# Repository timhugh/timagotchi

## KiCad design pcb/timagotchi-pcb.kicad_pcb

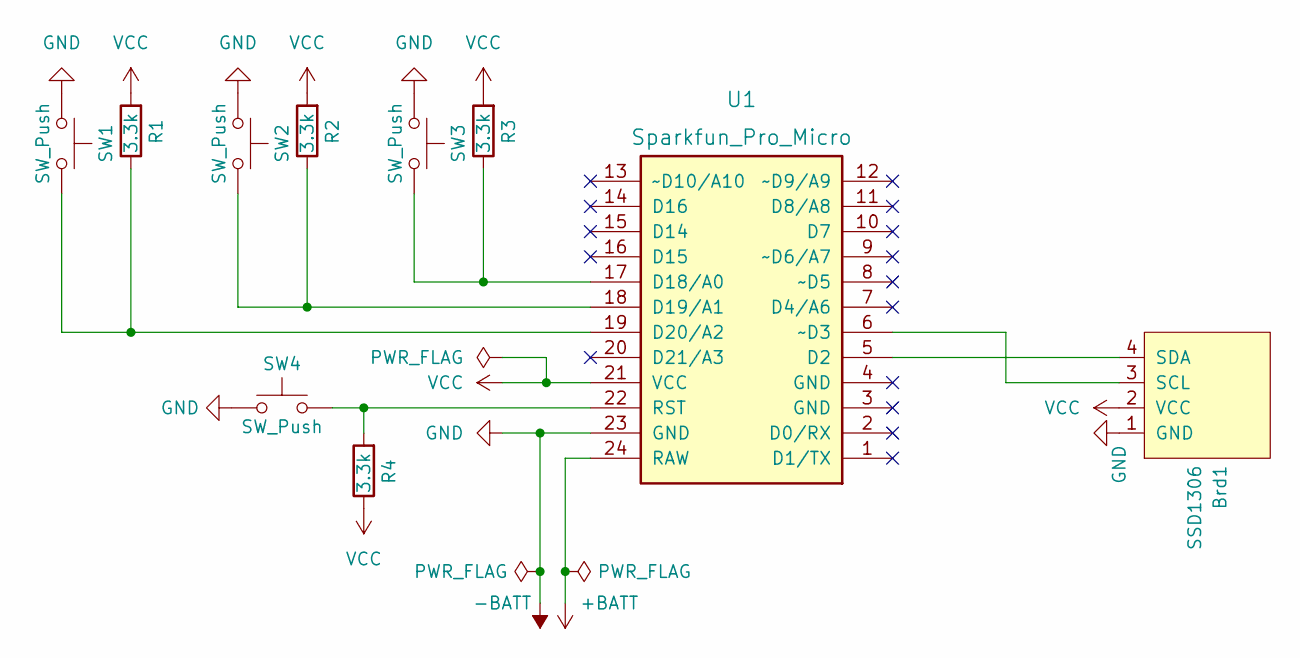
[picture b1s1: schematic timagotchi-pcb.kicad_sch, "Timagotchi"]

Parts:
Brd1: SSD1306; Adafruit_SSD1306_No_Mounting_Holes
R1, R2, R3, R4: 3.3k; R_0805_2012Metric
SW1, SW2, SW3, SW4: SW_Push; SW_PUSH_6mm
U1: Sparkfun_Pro_Micro

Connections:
+BATT: U1.24 (RAW)
-BATT: Brd1.1 (GND), SW1.2, SW2.2, SW3.2, SW4.2, U1.23 (GND)
unnamed: Brd1.3 (SCL), U1.6 (~D3)
unnamed: Brd1.4 (SDA), U1.5 (D2)
unnamed: R1.1, SW1.1, U1.19 (D20/A2)
unnamed: R2.1, SW2.1, U1.18 (D19/A1)
unnamed: R3.1, SW3.1, U1.17 (D18/A0)
unnamed: R4.2, SW4.1, U1.22 (RST)
VCC: Brd1.2 (VCC), R1.2, R2.2, R3.2, R4.1, U1.21 (VCC)

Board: 2 copper layers, 10 parts (0 on the bottom side), 8 nets, no tracks yet.

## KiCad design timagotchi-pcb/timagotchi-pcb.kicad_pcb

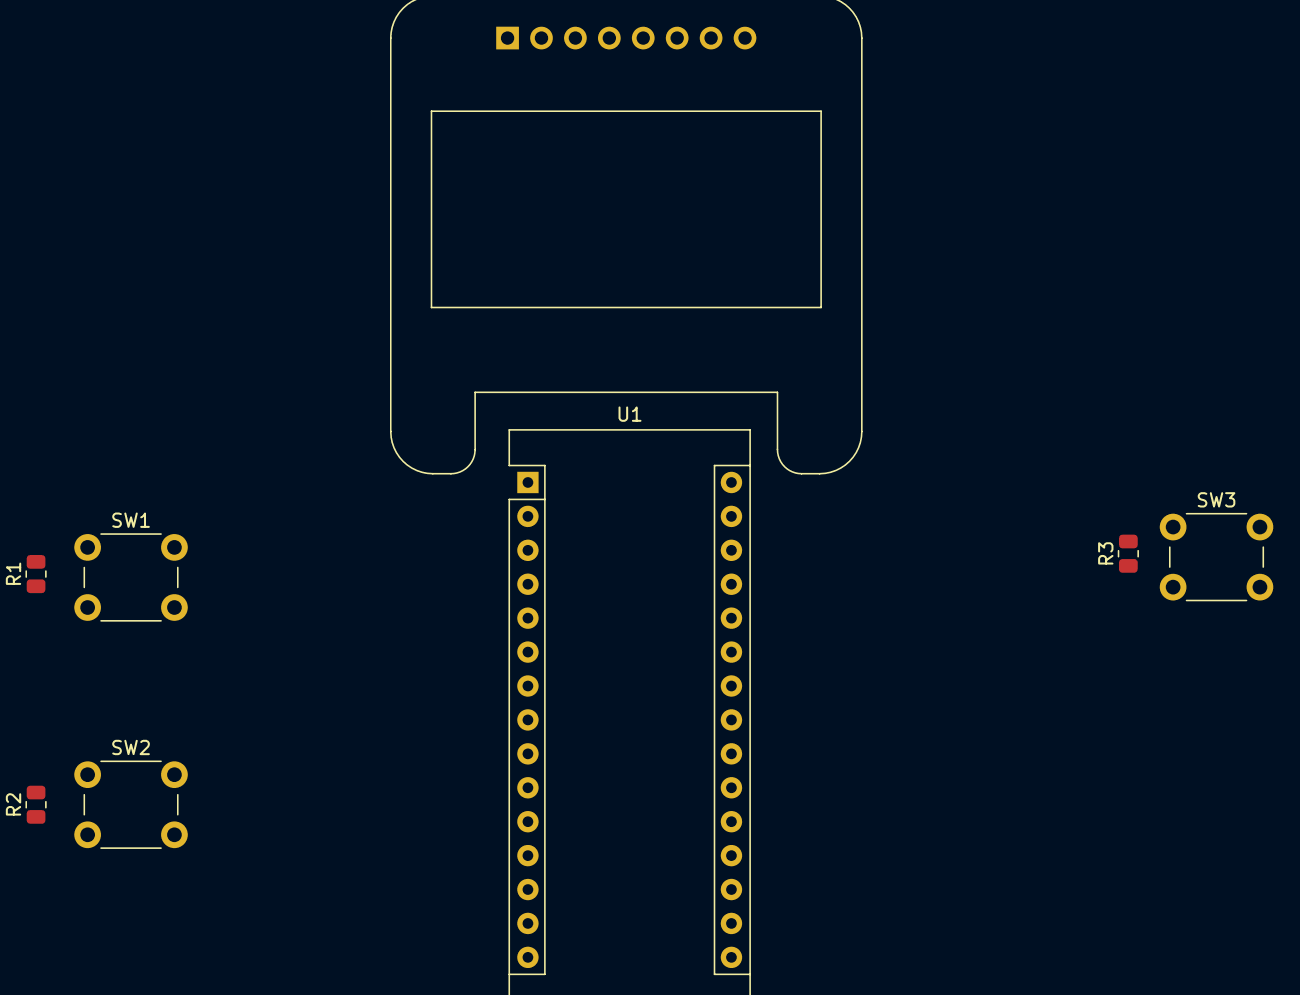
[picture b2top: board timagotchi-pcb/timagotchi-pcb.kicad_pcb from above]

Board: 2 copper layers, 8 parts (0 on the bottom side), 7 nets, no tracks yet.

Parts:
Brd1: SSD1306; Adafruit_SSD1306_No_Mounting_Holes
R1, R2: 10k; R_0805_2012Metric
R3: 3.3k; R_0805_2012Metric
SW1, SW2, SW3: SW_Push; SW_PUSH_6mm
U1: Arduino_Nano

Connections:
+5V: Brd1.2 (VCC), R3.1, SW1.2, SW2.2, U1.27 (+5V)
GND: Brd1.1 (GND), R1.2, R2.2, SW3.2, U1.4 (GND), U1.29 (GND)
unnamed: Brd1.3 (SCL), U1.24 (A5/D19)
unnamed: Brd1.4 (SDA), U1.23 (A4/D18)
unnamed: R3.2, SW3.1, U1.28 (~RESET)
unnamed: R1.1, SW1.1, U1.6 (~D3)
unnamed: R2.1, SW2.1, U1.7 (D4)

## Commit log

2022-05-31 new kicad project
2022-05-31 add promicro library
2022-05-31 add ssd1306 lib
2022-05-31 add arduino lib
2022-05-31 remove promicro lib
2022-05-31 schematic design
2022-05-31 use pwr_flag correctly, start pcb
2022-05-31 rename folder for gitmodules
2022-05-31 rename pcb folder
2022-05-31 readd kicad lib submodules
2022-05-31 new platformio project w/ blink script
2022-05-31 new kicad version did stuff to the schematic for whatever reason
2022-05-31 add code to test screen and buttons
2022-05-31 ignore kicad backups
2022-05-31 schematic v2
    switch to pro micro 3.3v
    * will be able to tune power lower
    * smaller footprint
    add third button
    change buttons from pulldown to pullup
2022-05-31 add missing pwr_flag
2022-06-01 remove autosave file
2022-06-01 balance resistors and gen new pcb
2022-06-01 rotate schematic
    usb north
